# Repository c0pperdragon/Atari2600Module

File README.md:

# Atari2600Module
Game module board for Atari 2600 that can hold 16 games.

After I have obtained and repaired an old Atari 2600 console (a "light sixer" PAL variant), 
I also wanted to use it with the top games of the time. Working game cartridges can still be found
on action platforms, but it is very difficult and expensive to get the famous ones. 
On the other hand, basically everything that was ever released for the Atari 2600 is available 
as rom images on the web (PAL variants included).

Since the electronics of those days was pretty easy to handle for hobbyist, making an own 
cartridge with an EPROM (can still be obtained in PID variants) and some small electronics parts
is possible for little money.

To keep it as cheap as possible, I have not created a PCB (don't have the equipment), but
used a standard board with two layers of copper lines and cut it to the proper shape with a jigsaw.
According to the sources on the topic the Atari 2600 uses a not-inverted signal to access the 
chip select line of the EPROM, so an inverter is also on the board.
The EPROM I found was a 64KByte variant, so it could hold 16 of the standard-sized 4 KByte 
game ROMs. Selecting is done with an 16-position encoder switch that directly drives the 
higher 4 address lines of the EPROM.

One of the greatest problems in this project was to burn the EPROM. It seems that EPROMs have
completely gone out of use this days and the programmers that can still be bought are extremely
expensive. For this one-off programming I have used my Arduino Micro with one additional 8-bit 
shift register to do the job. I improvised everything on breadboards for the task. Unfortunately 
I have no schematics or images of this left, only the programmer code is still available.

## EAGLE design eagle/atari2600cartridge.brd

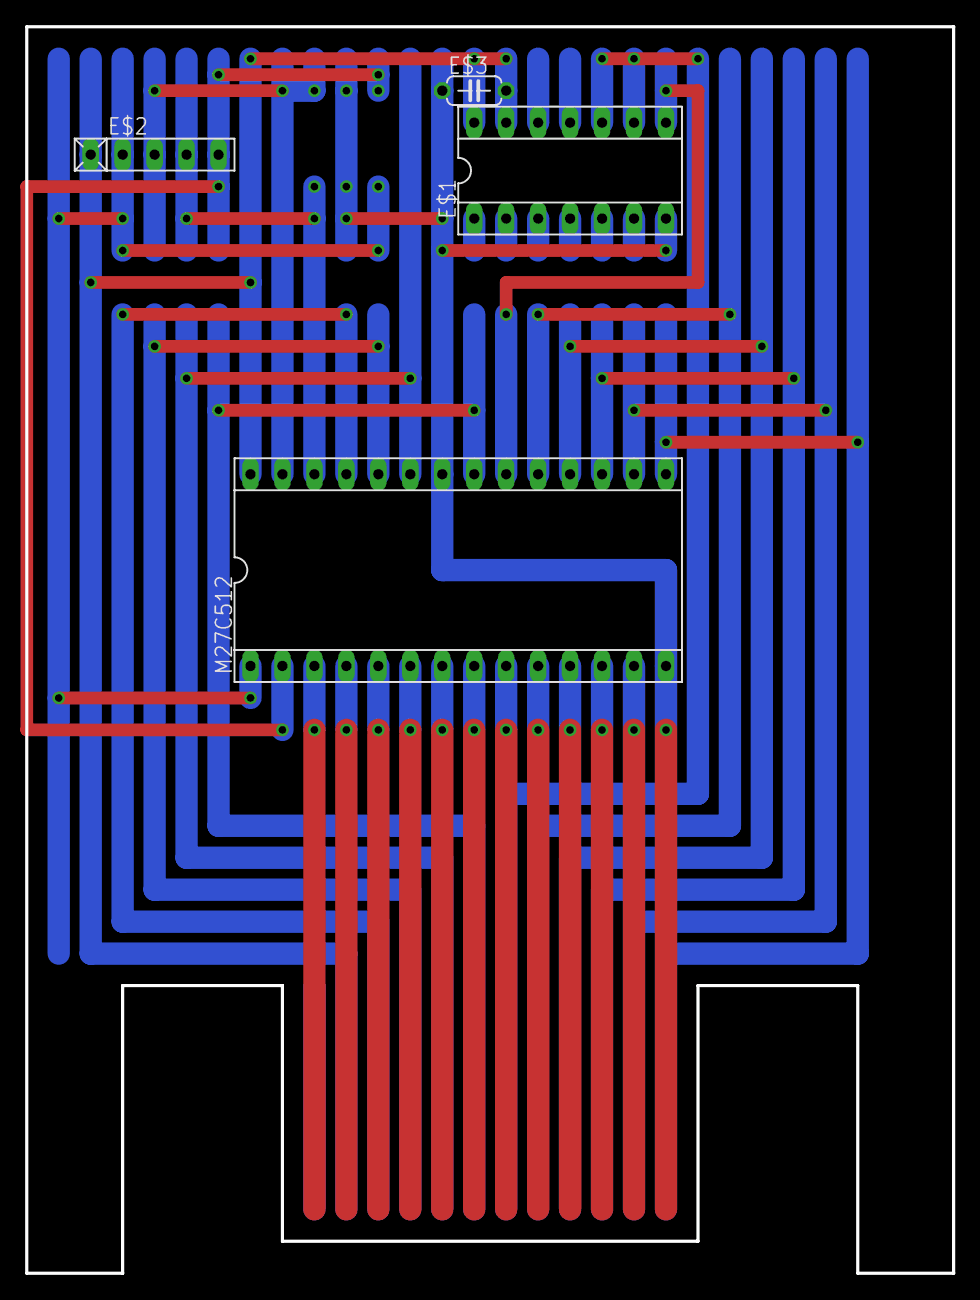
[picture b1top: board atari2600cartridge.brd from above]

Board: 2 copper layers, 73.7 x 99.1 mm, 4 parts (0 on the bottom side), 8 nets.

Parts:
E$1: SOCKET-14
E$2: RN-5
E$3: C050-024X044
M27C512: SOCKET-28-6

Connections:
5V: E$1.13, E$1.14, E$2.1, E$3.2, M27C512.28
A12: E$2.5, M27C512.2
A14: E$2.3, M27C512.27
A15: E$2.2, M27C512.1
CS: E$1.9, E$1.10
E: E$1.8, M27C512.20
GND: E$1.7, E$3.1, M27C512.14, M27C512.22
S$2: E$2.4, M27C512.26

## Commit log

2015-09-02 Upload for documentary purposes
2016-07-05 archive roms
2020-08-10 Circuit for compositve video from Atari 2600
